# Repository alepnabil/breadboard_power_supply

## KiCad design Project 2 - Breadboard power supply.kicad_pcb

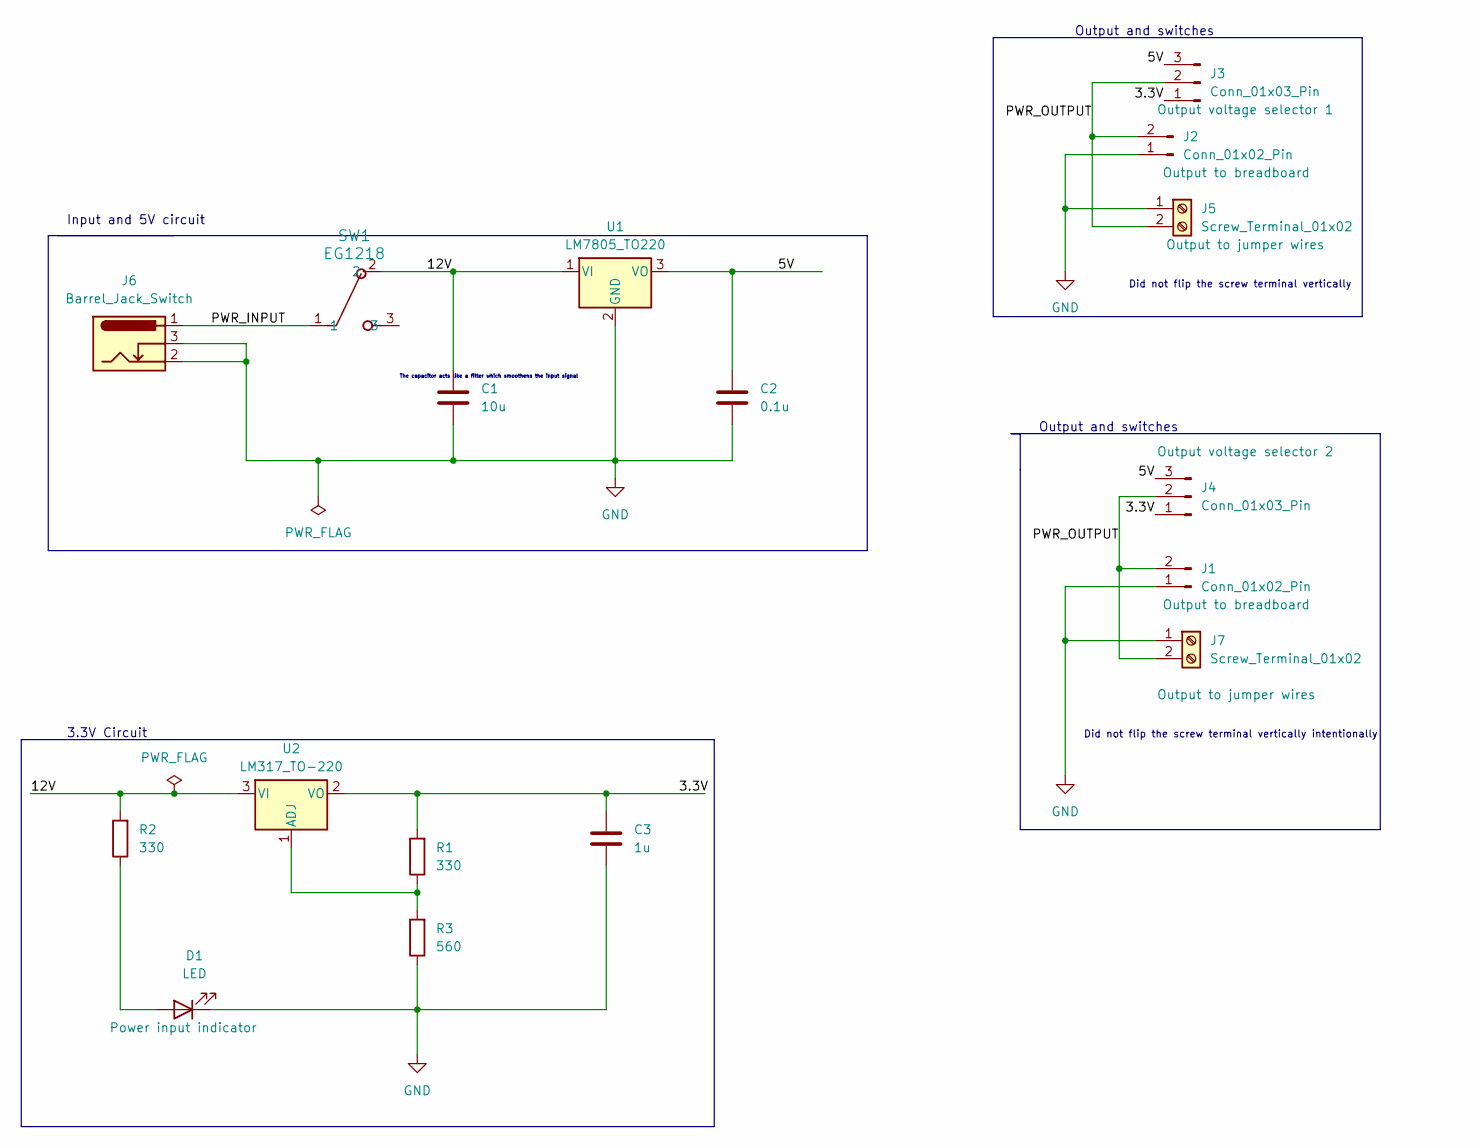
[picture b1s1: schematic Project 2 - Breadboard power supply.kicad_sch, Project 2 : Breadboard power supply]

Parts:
C1: 10u; PinHeader_1x02_P2.54mm_Vertical
C2: 0.1u; C_Disc_D3.0mm_W1.6mm_P2.50mm
C3: 1u; C_Disc_D3.0mm_W1.6mm_P2.50mm
D1: LED; LED_D5.0mm
J1, J2: Conn_01x02_Pin; PinHeader_1x02_P2.54mm_Vertical
J3, J4: Conn_01x03_Pin; PinHeader_1x02_P2.54mm_Vertical
J5, J7: Screw_Terminal_01x02; TerminalBlock_bornier-2_P5.08mm
J6: Barrel_Jack_Switch; BarrelJack_Horizontal
R1, R2: 330; R_Axial_DIN0207_L6.3mm_D2.5mm_P7.62mm_Horizontal
R3: 560; R_Axial_DIN0207_L6.3mm_D2.5mm_P7.62mm_Horizontal
SW1: EG1218; SW_1218_EWI
U1: LM7805_TO220; TO-220-3_Vertical
U2: LM317_TO-220; TO-220-3_Vertical

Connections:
/3.3V: C3.1, J3.1, J4.1, R1.2, U2.2 (VO)
/5V: C2.1, J3.3, J4.3, U1.3 (VO)
/12V: C1.1, R2.2, SW1.2, U1.1 (VI), U2.3 (VI)
/PWR_INPUT: J6.1, SW1.1
/PWR_OUTPUT: J1.2, J2.2, J3.2, J4.2, J5.2, J7.2
GND: C1.2, C2.2, C3.2, D1.1 (K), J1.1, J2.1, J5.1, J6.2, J6.3, J7.1, R3.1, U1.2 (GND)
unnamed: D1.2 (A), R2.1
unnamed: R1.1, R3.2, U2.1 (ADJ)

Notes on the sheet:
The capacitor acts like a filter which smoothens the input signal
3.3V Circuit
Output and switches
Did not flip the screw terminal vertically
Did not flip the screw terminal vertically intentionally
Input and 5V circuit

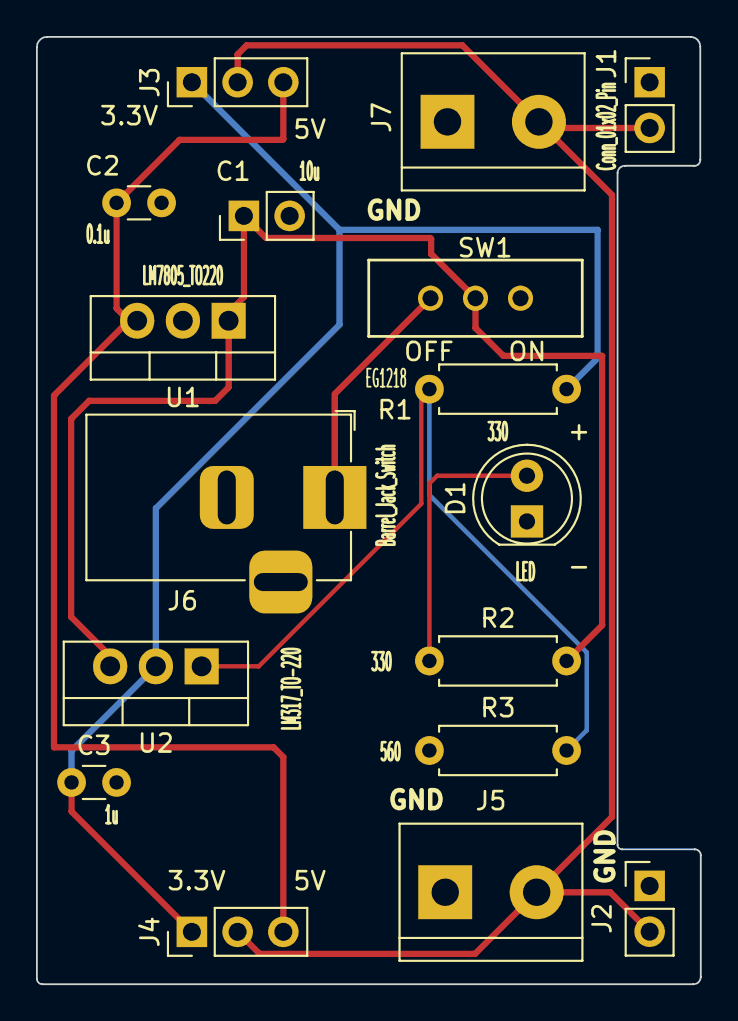
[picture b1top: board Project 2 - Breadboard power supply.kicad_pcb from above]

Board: 2 copper layers, 36.9 x 52.6 mm, 17 parts (0 on the bottom side), 8 nets.

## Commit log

2024-02-15 added gitignore file
2024-02-15 add updated schematic diagram with footprints
2024-02-15 added initial layout file
2024-02-15 add EG1218 switch symbols and footprints folder
2024-02-15 update edges with arch
2024-02-15 added routing and silkscreen
2024-02-15 exported gerber files
2024-02-15 make measurements
2024-02-15 fix power_output net label
